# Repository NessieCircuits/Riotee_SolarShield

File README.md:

# Riotee Solar Shield

The solar shield plugs into the headers of the [Riotee board](https://github.com/NessieCircuits/Riotee_Board). It has four small solar cells and a sliding switch to selectively switch on one, three, or all solar cells. This way you can experiment and see which configuration works best under the given light conditions.

Latest design files:

 - [Schematics](https://www.riotee.nessie-circuits.de/artifacts/solar_shield/latest/schematics.pdf)
 - [Layout](https://www.riotee.nessie-circuits.de/artifacts/solar_shield/latest/pcb.pdf)
 - [Rendering](https://www.riotee.nessie-circuits.de/artifacts/solar_shield/latest/3drendering.png "Riotee solar shield")
 - [Gerber](https://www.riotee.nessie-circuits.de/artifacts/solar_shield/latest/gerber.zip)
 - [BOM](https://www.riotee.nessie-circuits.de/artifacts/solar_shield/latest/bom.csv)

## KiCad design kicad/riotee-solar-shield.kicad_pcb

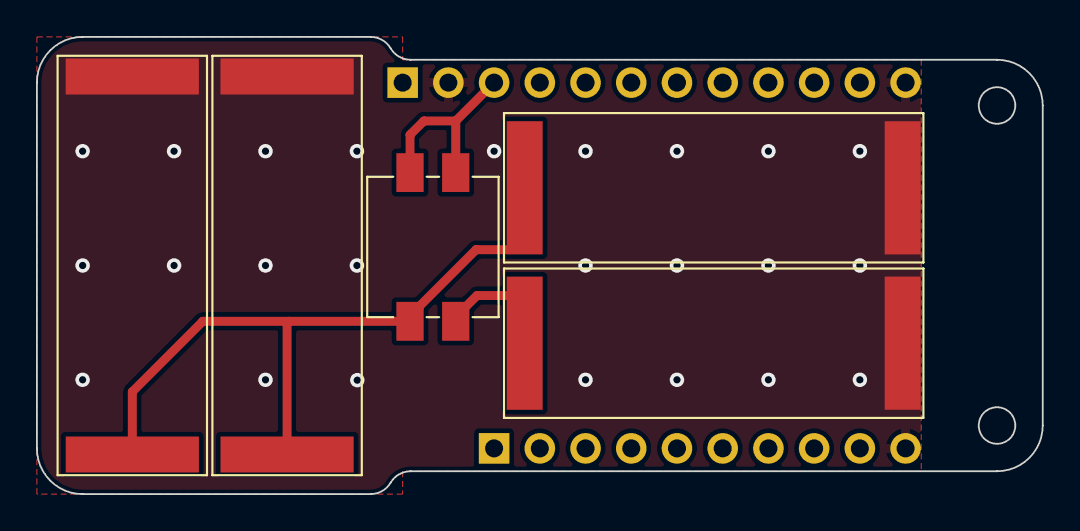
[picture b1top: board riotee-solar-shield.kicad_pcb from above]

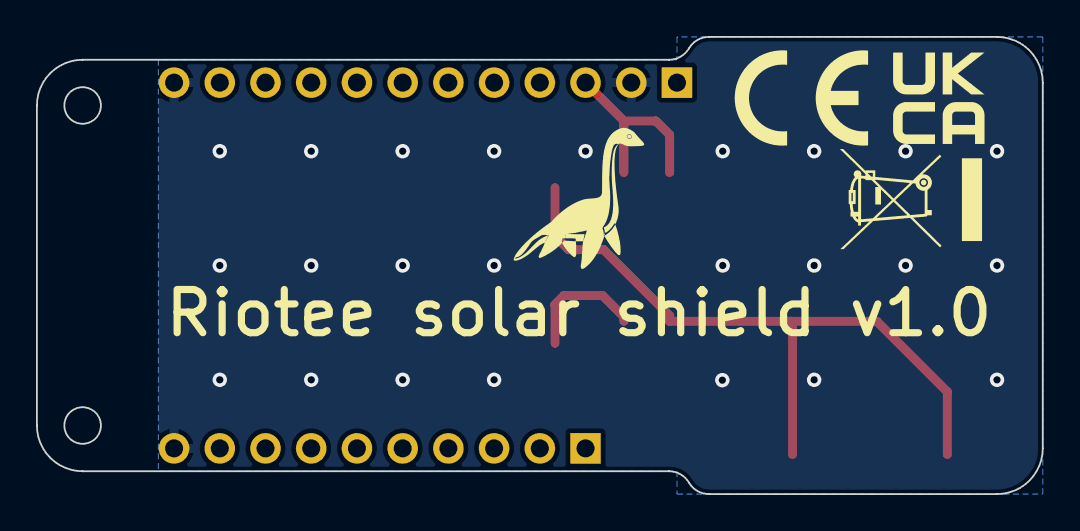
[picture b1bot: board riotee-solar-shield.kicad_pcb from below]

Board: 2 copper layers, 55.9 x 25.4 mm, 7 parts (2 on the bottom side), 4 nets.

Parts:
J1: Conn_01x10; PinHeader_1x10_P2.54mm_Vertical
J2: Conn_01x12; PinHeader_1x12_P2.54mm_Vertical
SC1, SC2, SC3, SC4: KXOB25-05X3F; AS_KXOB25_23x08
SW1: SW_DIP_x02; TE_1825058-1

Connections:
/Vharvester: J2.3, SW1.3, SW1.4
GND: J1.10, J2.2, J2.12, SC1.2 (-), SC2.2 (-), SC3.2 (-), SC4.2 (-)
unnamed: SC1.1 (+), SC2.1 (+), SC3.1 (+), SW1.1
unnamed: SC4.1 (+), SW1.2

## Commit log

2023-01-20 update footprints to fix missing 3d models
2023-01-20 add submodule checkout to github workflow
2023-02-20 add MPNs in schematics
2023-02-20 add assembly plan to CI/CD build
2023-02-24 add missing license
2023-02-24 new 3d model for solar panels
2023-02-24 colored model of TE_1825058-1 dip switch
2023-04-14 add conformity marks and refine BOM
2023-04-26 migrate project to kicad 7
2023-04-28 add kikit configuration for production panel
2023-04-28 add gitignore
2023-04-28 fix header location
2023-04-28 add kicad ERC/DRC github action
2024-06-26 increase panel frame width
2024-06-26 update to kicad 8
2024-10-15 generate bom and gerber in github workflow with kibot
2025-10-01 Switch to KXOB25-03x4F and update to KiCad 9
